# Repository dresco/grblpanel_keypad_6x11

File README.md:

# 6x11 keypad PCB

A 6x11 matrix keypad, designed for the reference grblPANEL implementation.

Each of the six rows has provision for ten 12x12mm through hole momentary tactile switches, and one 3.5mm screw terminal header for for panel mount or encoder switch inputs.

Each switch position has a series diode to prevent ghosting. Switch postions would be populated to suit the chosen front panel layout & keypad map.

Connection back to the main PCB is made through a 2x10 IDC header.

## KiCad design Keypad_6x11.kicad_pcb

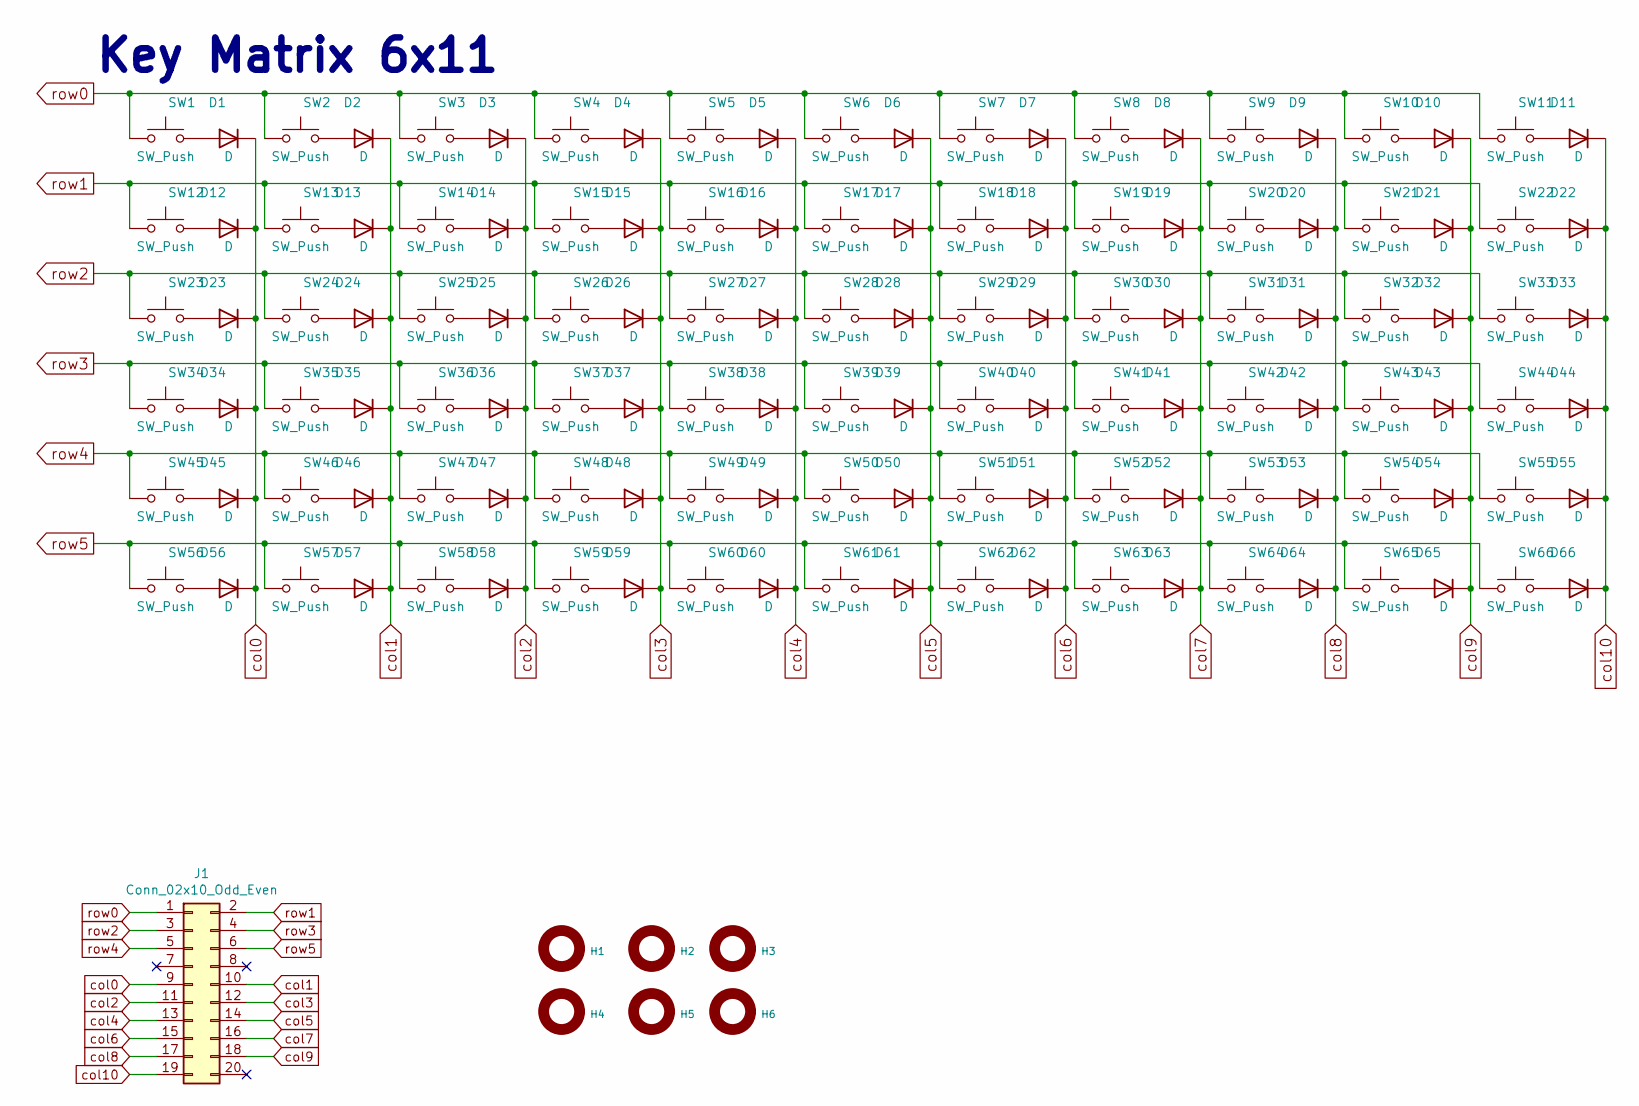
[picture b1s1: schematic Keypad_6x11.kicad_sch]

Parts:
D1, D2, D3, D4, D5, D6, D7, D8, D9, D10, D11, D12, D13, D14, D15, D16, D17, D18, D19, D20, D21, D22, D23, D24, D25, D26, D27, D28, D29, D30, D31, D32, D33, D34, D35, D36, D37, D38, D39, D40, D41, D42, D43, D44, D45, D46, D47, D48, D49, D50, D51, D52, D53, D54, D55, D56, D57, D58, D59, D60, D61, D62, D63, D64, D65, D66: D; D_SOD-323
H1, H2, H3, H4, H5, H6: HOLE; HOLE_3.2MM
J1: Conn_02x10_Odd_Even; IDC-Header_2x10_P2.54mm_Vertical
SW1, SW2, SW3, SW4, SW5, SW6, SW7, SW8, SW9, SW10, SW12, SW13, SW14, SW15, SW16, SW17, SW18, SW19, SW20, SW21, SW23, SW24, SW25, SW26, SW27, SW28, SW29, SW30, SW31, SW32, SW34, SW35, SW36, SW37, SW38, SW39, SW40, SW41, SW42, SW43, SW45, SW46, SW47, SW48, SW49, SW50, SW51, SW52, SW53, SW54, SW56, SW57, SW58, SW59, SW60, SW61, SW62, SW63, SW64, SW65: SW_Push; SW_PUSH_12MM
SW11, SW22, SW33, SW44, SW55, SW66: SW_Push; SCREW_TERMINAL_3.5MM_X2

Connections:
unnamed: D1.2 (A), SW1.2
unnamed: D2.2 (A), SW2.2
unnamed: D3.2 (A), SW3.2
unnamed: D4.2 (A), SW4.2
unnamed: D5.2 (A), SW5.2
unnamed: D6.2 (A), SW6.2
unnamed: D7.2 (A), SW7.2
unnamed: D8.2 (A), SW8.2
unnamed: D9.2 (A), SW9.2
unnamed: D10.2 (A), SW10.2
unnamed: D11.2 (A), SW11.2
unnamed: D12.2 (A), SW12.2
unnamed: D13.2 (A), SW13.2
unnamed: D14.2 (A), SW14.2
unnamed: D15.2 (A), SW15.2
unnamed: D16.2 (A), SW16.2
unnamed: D17.2 (A), SW17.2
unnamed: D18.2 (A), SW18.2
unnamed: D19.2 (A), SW19.2
unnamed: D20.2 (A), SW20.2
unnamed: D21.2 (A), SW21.2
unnamed: D22.2 (A), SW22.2
unnamed: D23.2 (A), SW23.2
unnamed: D24.2 (A), SW24.2
unnamed: D25.2 (A), SW25.2
unnamed: D26.2 (A), SW26.2
unnamed: D27.2 (A), SW27.2
unnamed: D28.2 (A), SW28.2
unnamed: D29.2 (A), SW29.2
unnamed: D30.2 (A), SW30.2
unnamed: D31.2 (A), SW31.2
unnamed: D32.2 (A), SW32.2
unnamed: D33.2 (A), SW33.2
unnamed: D34.2 (A), SW34.2
unnamed: D35.2 (A), SW35.2
unnamed: D36.2 (A), SW36.2
unnamed: D37.2 (A), SW37.2
unnamed: D38.2 (A), SW38.2
unnamed: D39.2 (A), SW39.2
unnamed: D40.2 (A), SW40.2
unnamed: D41.2 (A), SW41.2
unnamed: D42.2 (A), SW42.2
unnamed: D43.2 (A), SW43.2
unnamed: D44.2 (A), SW44.2
unnamed: D45.2 (A), SW45.2
unnamed: D46.2 (A), SW46.2
unnamed: D47.2 (A), SW47.2
unnamed: D48.2 (A), SW48.2
unnamed: D49.2 (A), SW49.2
unnamed: D50.2 (A), SW50.2
unnamed: D51.2 (A), SW51.2
unnamed: D52.2 (A), SW52.2
unnamed: D53.2 (A), SW53.2
unnamed: D54.2 (A), SW54.2
unnamed: D55.2 (A), SW55.2
unnamed: D56.2 (A), SW56.2
unnamed: D57.2 (A), SW57.2
unnamed: D58.2 (A), SW58.2
unnamed: D59.2 (A), SW59.2
unnamed: D60.2 (A), SW60.2
unnamed: D61.2 (A), SW61.2
unnamed: D62.2 (A), SW62.2
unnamed: D63.2 (A), SW63.2
unnamed: D64.2 (A), SW64.2
unnamed: D65.2 (A), SW65.2
unnamed: D66.2 (A), SW66.2
col0: D1.1 (K), D12.1 (K), D23.1 (K), D34.1 (K), D45.1 (K), D56.1 (K), J1.9
col1: D2.1 (K), D13.1 (K), D24.1 (K), D35.1 (K), D46.1 (K), D57.1 (K), J1.10
col2: D3.1 (K), D14.1 (K), D25.1 (K), D36.1 (K), D47.1 (K), D58.1 (K), J1.11
col3: D4.1 (K), D15.1 (K), D26.1 (K), D37.1 (K), D48.1 (K), D59.1 (K), J1.12
col4: D5.1 (K), D16.1 (K), D27.1 (K), D38.1 (K), D49.1 (K), D60.1 (K), J1.13
col5: D6.1 (K), D17.1 (K), D28.1 (K), D39.1 (K), D50.1 (K), D61.1 (K), J1.14
col6: D7.1 (K), D18.1 (K), D29.1 (K), D40.1 (K), D51.1 (K), D62.1 (K), J1.15
col7: D8.1 (K), D19.1 (K), D30.1 (K), D41.1 (K), D52.1 (K), D63.1 (K), J1.16
col8: D9.1 (K), D20.1 (K), D31.1 (K), D42.1 (K), D53.1 (K), D64.1 (K), J1.17
col9: D10.1 (K), D21.1 (K), D32.1 (K), D43.1 (K), D54.1 (K), D65.1 (K), J1.18
col10: D11.1 (K), D22.1 (K), D33.1 (K), D44.1 (K), D55.1 (K), D66.1 (K), J1.19
row0: J1.1, SW1.1, SW2.1, SW3.1, SW4.1, SW5.1, SW6.1, SW7.1, SW8.1, SW9.1, SW10.1, SW11.1
row1: J1.2, SW12.1, SW13.1, SW14.1, SW15.1, SW16.1, SW17.1, SW18.1, SW19.1, SW20.1, SW21.1, SW22.1
row2: J1.3, SW23.1, SW24.1, SW25.1, SW26.1, SW27.1, SW28.1, SW29.1, SW30.1, SW31.1, SW32.1, SW33.1
row3: J1.4, SW34.1, SW35.1, SW36.1, SW37.1, SW38.1, SW39.1, SW40.1, SW41.1, SW42.1, SW43.1, SW44.1
row4: J1.5, SW45.1, SW46.1, SW47.1, SW48.1, SW49.1, SW50.1, SW51.1, SW52.1, SW53.1, SW54.1, SW55.1
row5: J1.6, SW56.1, SW57.1, SW58.1, SW59.1, SW60.1, SW61.1, SW62.1, SW63.1, SW64.1, SW65.1, SW66.1

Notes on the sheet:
Key Matrix 6x11

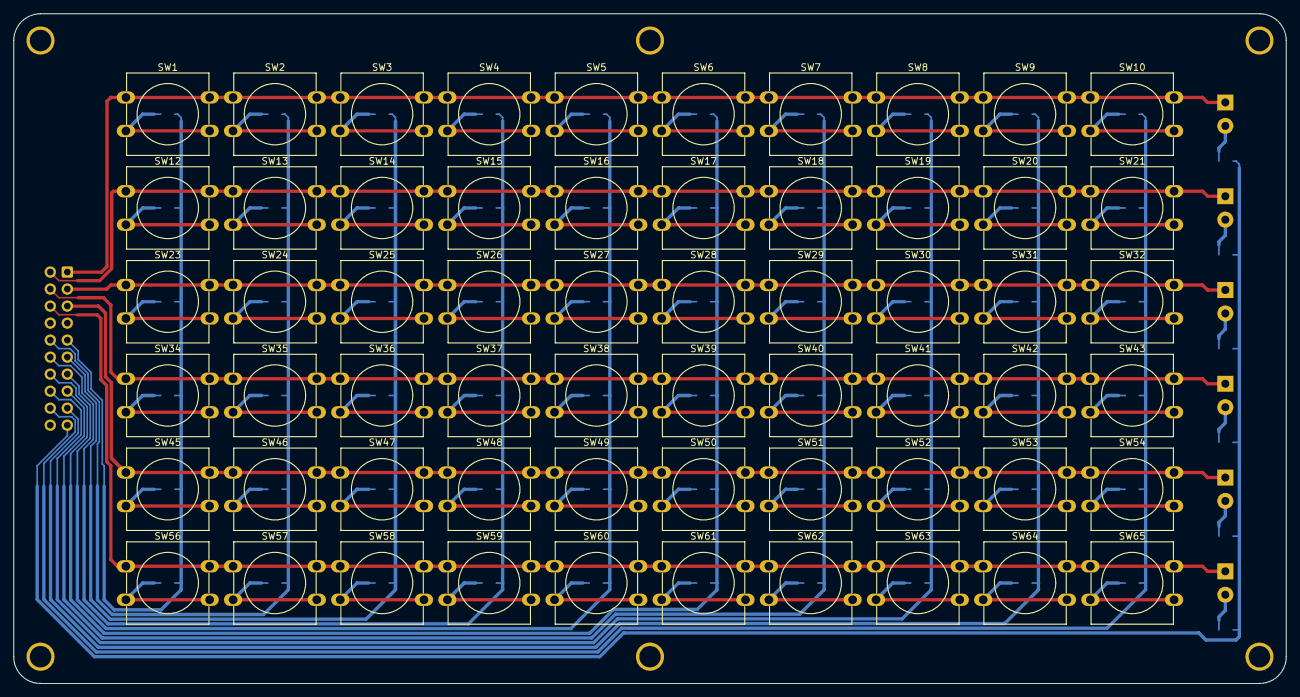
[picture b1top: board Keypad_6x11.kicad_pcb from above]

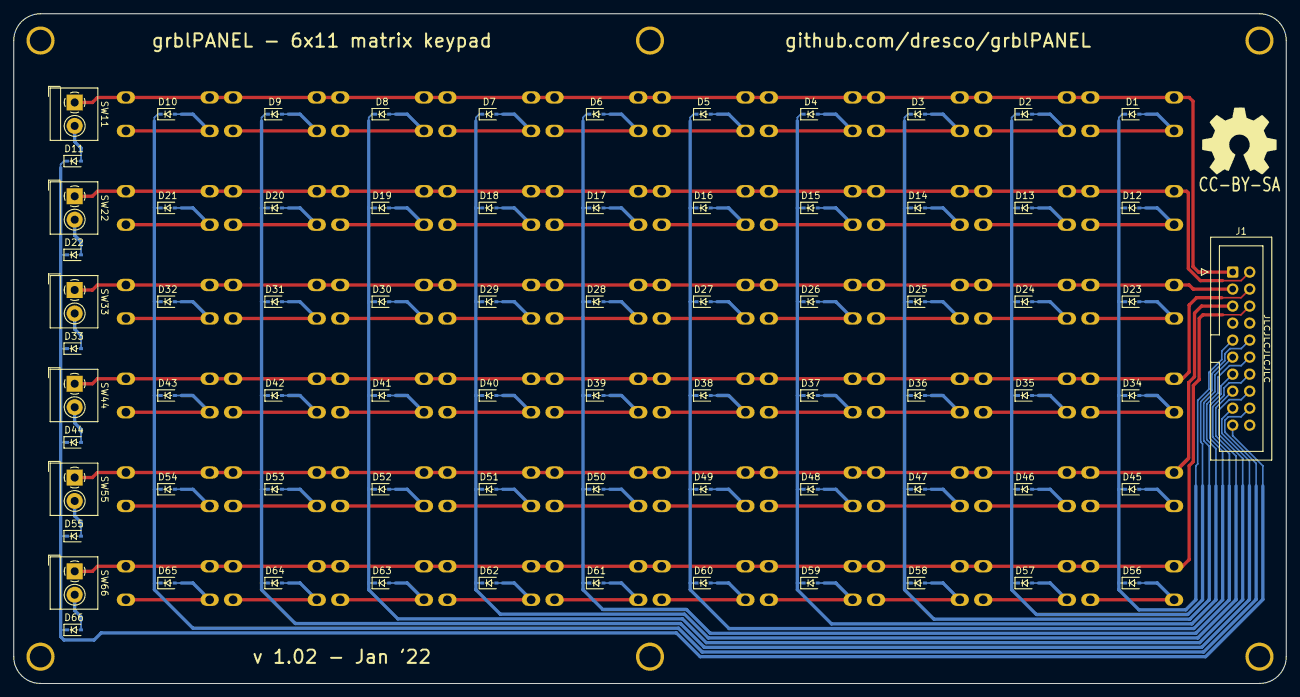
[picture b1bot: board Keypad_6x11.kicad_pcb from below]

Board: 2 copper layers, 190.0 x 100.0 mm, 139 parts (73 on the bottom side), 83 nets.

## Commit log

2022-01-02 Initial commit of 6x11 matrix keypad
2022-01-02 Adding manufacturing outputs
2022-01-03 Switch to smaller SOD-323 diode footprint for SMT assembly
2022-01-03 Add OSHW logo, rounded board corners
2022-01-03 v1.02 updates for manufacturing
2023-06-06 Commit minor schematic symbol updates
2023-06-06 Documentation update

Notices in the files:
Keypad_6x11.kicad_pcb:
CC-BY-SA
